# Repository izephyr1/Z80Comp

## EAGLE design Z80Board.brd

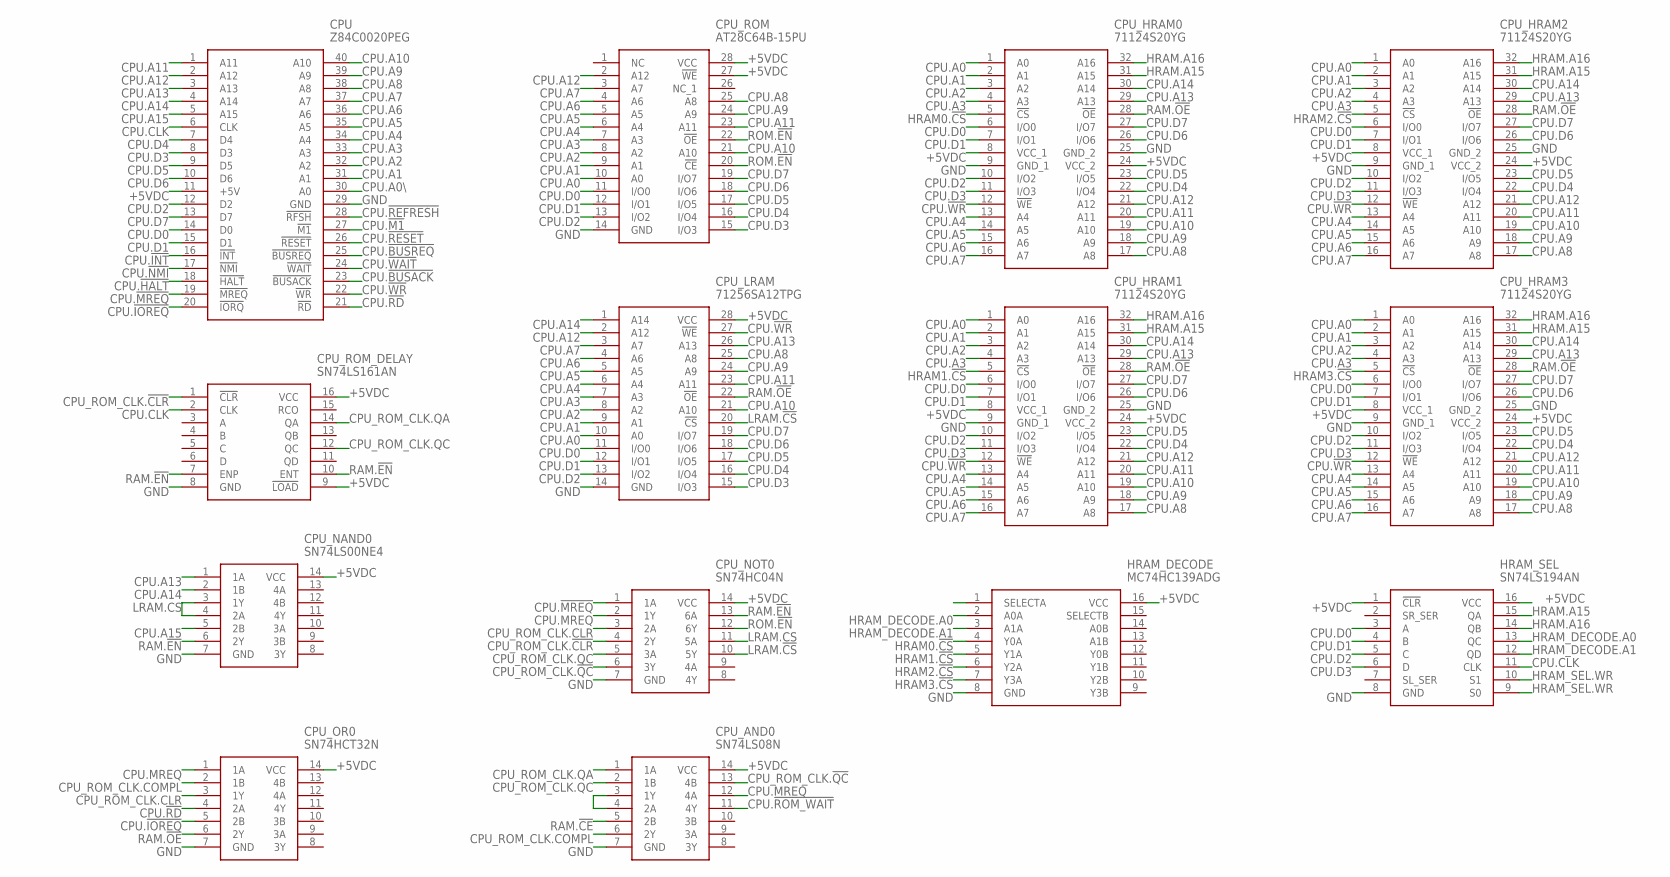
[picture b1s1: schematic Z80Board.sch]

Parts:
CPU: Z84C0020PEG; DIP1612W53P254L5232H406Q40N
CPU_AND0: SN74LS08N; DIP794W53P254L1930H508Q14N
CPU_HRAM0, CPU_HRAM1, CPU_HRAM2, CPU_HRAM3: 71124S20YG
CPU_LRAM: 71256SA12TPG; DIP851W46P254L3556H330Q28N
CPU_NAND0: SN74LS00NE4; DIP794W53P254L1930H508Q14N
CPU_NOT0: SN74HC04N; DIP794W53P254L1930H508Q14N
CPU_OR0: SN74HCT32N; DIP794W53P254L1930H508Q14N
CPU_ROM: AT28C64B-15PU; DIP1556W56P254L3702H483Q28N
CPU_ROM_DELAY: SN74LS161AN; DIP794W53P254L1930H508Q16N
HRAM_DECODE: MC74HC139ADG; SOIC127P600X175-16N
HRAM_SEL: SN74LS194AN; DIP794W53P254L1930H508Q16N

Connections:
+5VDC: CPU.11 (+5V), CPU_AND0.14 (VCC), CPU_HRAM0.8 (VCC_1), CPU_HRAM0.24 (VCC_2), CPU_HRAM1.8 (VCC_1), CPU_HRAM1.24 (VCC_2), CPU_HRAM2.8 (VCC_1), CPU_HRAM2.24 (VCC_2), CPU_HRAM3.8 (VCC_1), CPU_HRAM3.24 (VCC_2), CPU_LRAM.28 (VCC), CPU_NAND0.14 (VCC), CPU_NOT0.14 (VCC), CPU_OR0.14 (VCC), CPU_ROM.27 (!WE), CPU_ROM.28 (VCC), CPU_ROM_DELAY.9 (!LOAD), CPU_ROM_DELAY.16 (VCC), HRAM_DECODE.16 (VCC), HRAM_SEL.1 (!CLR), HRAM_SEL.16 (VCC)
CPU.!BUSACK: CPU.23 (!BUSACK)
CPU.!BUSREQ: CPU.25 (!BUSREQ)
CPU.!HALT: CPU.18 (!HALT)
CPU.!INT: CPU.16 (!INT)
CPU.!IOREQ: CPU.20 (!IORQ), CPU_OR0.5 (2B)
CPU.!M1: CPU.27 (!M1)
CPU.!MREQ: CPU.19 (!MREQ), CPU_NOT0.1 (1A)
CPU.!NMI: CPU.17 (!NMI)
CPU.!RD: CPU.21 (!RD), CPU_OR0.4 (2A)
CPU.!REFRESH: CPU.28 (!RFSH)
CPU.!RESET: CPU.26 (!RESET)
CPU.!ROM_WAIT: CPU_AND0.11 (4Y)
CPU.!WAIT: CPU.24 (!WAIT)
CPU.!WR: CPU.22 (!WR), CPU_HRAM0.12 (!WE), CPU_HRAM1.12 (!WE), CPU_HRAM2.12 (!WE), CPU_HRAM3.12 (!WE), CPU_LRAM.27 (!WE)
CPU.A0: CPU_HRAM0.1 (A0), CPU_HRAM1.1 (A0), CPU_HRAM2.1 (A0), CPU_HRAM3.1 (A0), CPU_LRAM.10 (A0), CPU_ROM.10 (A0)
CPU.A0\: CPU.30 (A0)
CPU.A1: CPU.31 (A1), CPU_HRAM0.2 (A1), CPU_HRAM1.2 (A1), CPU_HRAM2.2 (A1), CPU_HRAM3.2 (A1), CPU_LRAM.9 (A1), CPU_ROM.9 (A1)
CPU.A2: CPU.32 (A2), CPU_HRAM0.3 (A2), CPU_HRAM1.3 (A2), CPU_HRAM2.3 (A2), CPU_HRAM3.3 (A2), CPU_LRAM.8 (A2), CPU_ROM.8 (A2)
CPU.A3: CPU.33 (A3), CPU_HRAM0.4 (A3), CPU_HRAM1.4 (A3), CPU_HRAM2.4 (A3), CPU_HRAM3.4 (A3), CPU_LRAM.7 (A3), CPU_ROM.7 (A3)
CPU.A4: CPU.34 (A4), CPU_HRAM0.13 (A4), CPU_HRAM1.13 (A4), CPU_HRAM2.13 (A4), CPU_HRAM3.13 (A4), CPU_LRAM.6 (A4), CPU_ROM.6 (A4)
CPU.A5: CPU.35 (A5), CPU_HRAM0.14 (A5), CPU_HRAM1.14 (A5), CPU_HRAM2.14 (A5), CPU_HRAM3.14 (A5), CPU_LRAM.5 (A5), CPU_ROM.5 (A5)
CPU.A6: CPU.36 (A6), CPU_HRAM0.15 (A6), CPU_HRAM1.15 (A6), CPU_HRAM2.15 (A6), CPU_HRAM3.15 (A6), CPU_LRAM.4 (A6), CPU_ROM.4 (A6)
CPU.A7: CPU.37 (A7), CPU_HRAM0.16 (A7), CPU_HRAM1.16 (A7), CPU_HRAM2.16 (A7), CPU_HRAM3.16 (A7), CPU_LRAM.3 (A7), CPU_ROM.3 (A7)
CPU.A8: CPU.38 (A8), CPU_HRAM0.17 (A8), CPU_HRAM1.17 (A8), CPU_HRAM2.17 (A8), CPU_HRAM3.17 (A8), CPU_LRAM.25 (A8), CPU_ROM.25 (A8)
CPU.A9: CPU.39 (A9), CPU_HRAM0.18 (A9), CPU_HRAM1.18 (A9), CPU_HRAM2.18 (A9), CPU_HRAM3.18 (A9), CPU_LRAM.24 (A9), CPU_ROM.24 (A9)
CPU.A10: CPU.40 (A10), CPU_HRAM0.19 (A10), CPU_HRAM1.19 (A10), CPU_HRAM2.19 (A10), CPU_HRAM3.19 (A10), CPU_LRAM.21 (A10), CPU_ROM.21 (A10)
CPU.A11: CPU.1 (A11), CPU_HRAM0.20 (A11), CPU_HRAM1.20 (A11), CPU_HRAM2.20 (A11), CPU_HRAM3.20 (A11), CPU_LRAM.23 (A11), CPU_ROM.23 (A11)
CPU.A12: CPU.2 (A12), CPU_HRAM0.21 (A12), CPU_HRAM1.21 (A12), CPU_HRAM2.21 (A12), CPU_HRAM3.21 (A12), CPU_LRAM.2 (A12), CPU_ROM.2 (A12)
CPU.A13: CPU.3 (A13), CPU_HRAM0.29 (A13), CPU_HRAM1.29 (A13), CPU_HRAM2.29 (A13), CPU_HRAM3.29 (A13), CPU_LRAM.26 (A13), CPU_NAND0.1 (1A)
CPU.A14: CPU.4 (A14), CPU_HRAM0.30 (A14), CPU_HRAM1.30 (A14), CPU_HRAM2.30 (A14), CPU_HRAM3.30 (A14), CPU_LRAM.1 (A14), CPU_NAND0.2 (1B)
CPU.A15: CPU.5 (A15), CPU_NAND0.5 (2B)
CPU.CLK: CPU.6 (CLK), CPU_ROM_DELAY.2 (CLK), HRAM_SEL.11 (CLK)
CPU.D0: CPU.14 (D0), CPU_HRAM0.6 (I/O0), CPU_HRAM1.6 (I/O0), CPU_HRAM2.6 (I/O0), CPU_HRAM3.6 (I/O0), CPU_LRAM.11 (I/O0), CPU_ROM.11 (I/O0), HRAM_SEL.3 (A)
CPU.D1: CPU.15 (D1), CPU_HRAM0.7 (I/O1), CPU_HRAM1.7 (I/O1), CPU_HRAM2.7 (I/O1), CPU_HRAM3.7 (I/O1), CPU_LRAM.12 (I/O1), CPU_ROM.12 (I/O1), HRAM_SEL.4 (B)
CPU.D2: CPU.12 (D2), CPU_HRAM0.10 (I/O2), CPU_HRAM1.10 (I/O2), CPU_HRAM2.10 (I/O2), CPU_HRAM3.10 (I/O2), CPU_LRAM.13 (I/O2), CPU_ROM.13 (I/O2), HRAM_SEL.5 (C)
CPU.D3: CPU.8 (D3), CPU_HRAM0.11 (I/O3), CPU_HRAM1.11 (I/O3), CPU_HRAM2.11 (I/O3), CPU_HRAM3.11 (I/O3), CPU_LRAM.15 (I/O3), CPU_ROM.15 (I/O3), HRAM_SEL.6 (D)
CPU.D4: CPU.7 (D4), CPU_HRAM0.22 (I/O4), CPU_HRAM1.22 (I/O4), CPU_HRAM2.22 (I/O4), CPU_HRAM3.22 (I/O4), CPU_LRAM.16 (I/O4), CPU_ROM.16 (I/O4)
CPU.D5: CPU.9 (D5), CPU_HRAM0.23 (I/O5), CPU_HRAM1.23 (I/O5), CPU_HRAM2.23 (I/O5), CPU_HRAM3.23 (I/O5), CPU_LRAM.17 (I/O5), CPU_ROM.17 (I/O5)
CPU.D6: CPU.10 (D6), CPU_HRAM0.26 (I/O6), CPU_HRAM1.26 (I/O6), CPU_HRAM2.26 (I/O6), CPU_HRAM3.26 (I/O6), CPU_LRAM.18 (I/O6), CPU_ROM.18 (I/O6)
CPU.D7: CPU.13 (D7), CPU_HRAM0.27 (I/O7), CPU_HRAM1.27 (I/O7), CPU_HRAM2.27 (I/O7), CPU_HRAM3.27 (I/O7), CPU_LRAM.19 (I/O7), CPU_ROM.19 (I/O7)
CPU.MREQ: CPU_AND0.12 (4A), CPU_NOT0.2 (1Y), CPU_OR0.1 (1A)
CPU_ROM_CLK.!CLR: CPU_NOT0.4 (2Y), CPU_ROM_DELAY.1 (!CLR)
CPU_ROM_CLK.!QC: CPU_AND0.13 (4B), CPU_NOT0.6 (3Y)
CPU_ROM_CLK.CLR: CPU_NOT0.3 (2A), CPU_OR0.3 (1Y)
CPU_ROM_CLK.COMPL: CPU_AND0.6 (2Y), CPU_OR0.2 (1B)
CPU_ROM_CLK.QA: CPU_AND0.1 (1A), CPU_ROM_DELAY.14 (QA)
CPU_ROM_CLK.QC: CPU_AND0.2 (1B), CPU_NOT0.5 (3A), CPU_ROM_DELAY.12 (QC)
GND: CPU.29 (GND), CPU_AND0.7 (GND), CPU_HRAM0.9 (GND_1), CPU_HRAM0.25 (GND_2), CPU_HRAM1.9 (GND_1), CPU_HRAM1.25 (GND_2), CPU_HRAM2.9 (GND_1), CPU_HRAM2.25 (GND_2), CPU_HRAM3.9 (GND_1), CPU_HRAM3.25 (GND_2), CPU_LRAM.14 (GND), CPU_NAND0.7 (GND), CPU_NOT0.7 (GND), CPU_OR0.7 (GND), CPU_ROM.14 (GND), CPU_ROM_DELAY.8 (GND), HRAM_DECODE.8 (GND), HRAM_SEL.8 (GND)
HRAM0.!CS: CPU_HRAM0.5 (!CS), HRAM_DECODE.4 (Y0A)
HRAM1.!CS: CPU_HRAM1.5 (!CS), HRAM_DECODE.5 (Y1A)
HRAM2.!CS: CPU_HRAM2.5 (!CS), HRAM_DECODE.6 (Y2A)
HRAM3.!CS: CPU_HRAM3.5 (!CS), HRAM_DECODE.7 (Y3A)
HRAM.A15: CPU_HRAM0.31 (A15), CPU_HRAM1.31 (A15), CPU_HRAM2.31 (A15), CPU_HRAM3.31 (A15), HRAM_SEL.15 (QA)
HRAM.A16: CPU_HRAM0.32 (A16), CPU_HRAM1.32 (A16), CPU_HRAM2.32 (A16), CPU_HRAM3.32 (A16), HRAM_SEL.14 (QB)
HRAM_DECODE.A0: HRAM_DECODE.2 (A0A), HRAM_SEL.13 (QC)
HRAM_DECODE.A1: HRAM_DECODE.3 (A1A), HRAM_SEL.12 (QD)
HRAM_SEL.WR: HRAM_SEL.9 (S0), HRAM_SEL.10 (S1)
LRAM.!CS: CPU_LRAM.20 (!CS), CPU_NOT0.10 (5Y)
LRAM.CS: CPU_NAND0.3 (1Y), CPU_NAND0.4 (2A), CPU_NOT0.11 (5A)
unnamed: CPU_AND0.3 (1Y), CPU_AND0.4 (2A)
RAM.!CE: CPU_AND0.5 (2B)
RAM.!EN: CPU_NAND0.6 (2Y), CPU_NOT0.13 (6A), CPU_ROM_DELAY.7 (ENP), CPU_ROM_DELAY.10 (ENT)
RAM.!OE: CPU_HRAM0.28 (!OE), CPU_HRAM1.28 (!OE), CPU_HRAM2.28 (!OE), CPU_HRAM3.28 (!OE), CPU_LRAM.22 (!OE), CPU_OR0.6 (2Y)
ROM.!EN: CPU_NOT0.12 (6Y), CPU_ROM.20 (!CE), CPU_ROM.22 (!OE)

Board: 2 copper layers, 14 parts (0 on the bottom side), 53 nets, no tracks yet.
